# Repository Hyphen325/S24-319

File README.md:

This project is all of the lab work from ECE 319k and it's associated projects

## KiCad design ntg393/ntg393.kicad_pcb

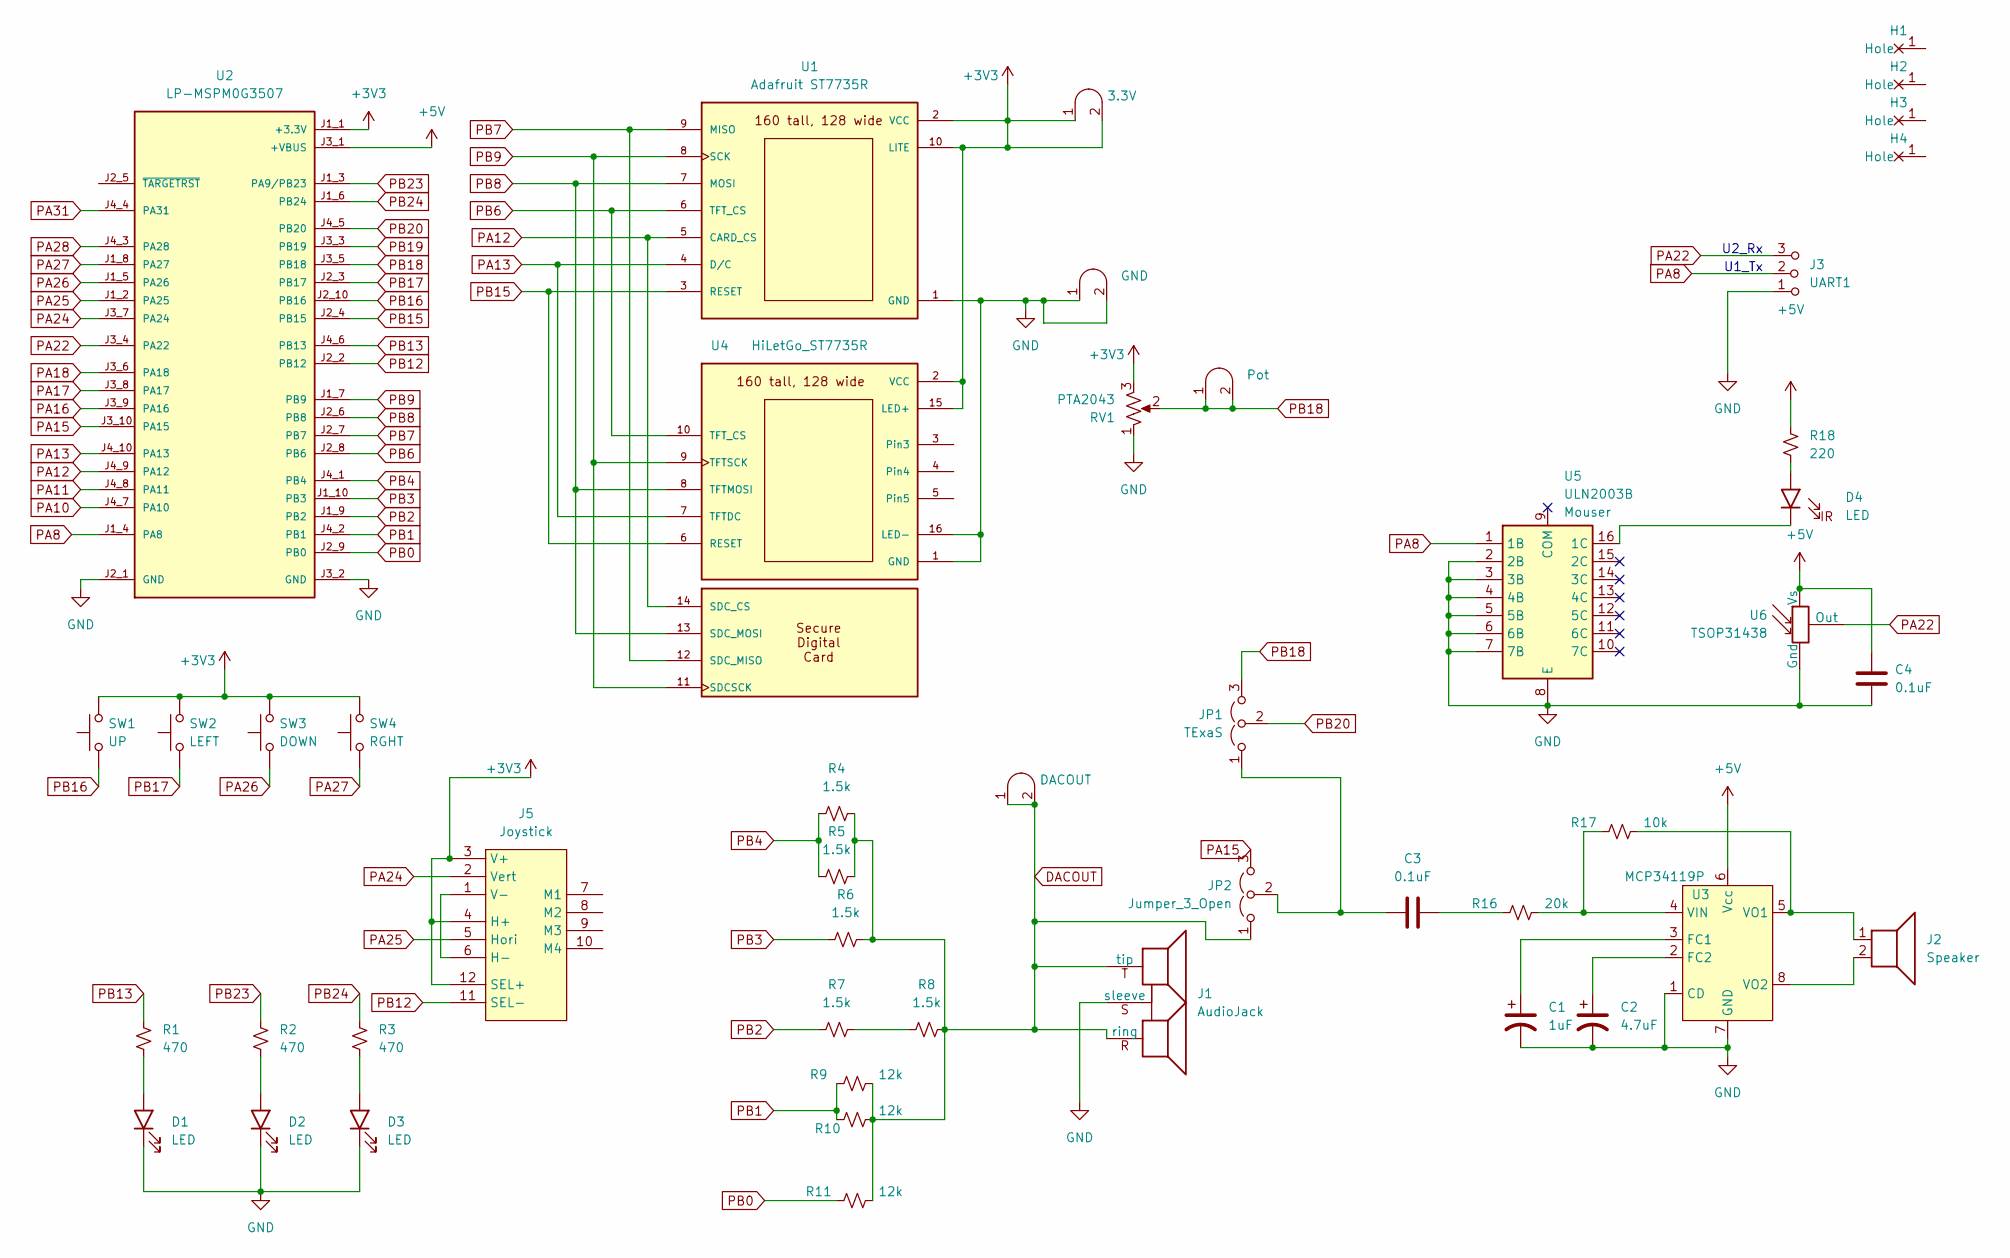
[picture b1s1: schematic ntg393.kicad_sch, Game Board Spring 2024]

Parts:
C1: 1uF; CP_Radial_Tantal200mil
C2: 4.7uF; CP_Radial_Tantal200mil
C3, C4: 0.1uF; C_Axial_200mil
D1, D2, D3, D4: LED; LED_D5.0mm
H1, H2, H3, H4: MountingHole_4_40
J1: AudioJack; Jack_3.5mm_CUI_SJ1-3523N_Horizontal
J2: Speaker; PinHeader_1x02_P2.54mm_Vertical
J3: UART1; PinHeader_1x03_P2.54mm_Vertical
J4: Pot; Testpoint_1x02_P2.54mm
J5: Joystick; SparkfunJoystick
J6: GND; Testpoint_1x02_P2.54mm
J7: DACOUT; Testpoint_1x02_P2.54mm
JP1: TExaS; PinHeader_1x03_P2.54mm_Vertical
JP2: Jumper_3_Open; PinHeader_1x03_P2.54mm_Vertical
R1, R2, R3: 470; R_Axial_DIN0204_L3.6mm_D1.6mm_P7.62mm_Horizontal
R4, R5, R6, R7, R8: 1.5k; R_Axial_DIN0204_L3.6mm_D1.6mm_P7.62mm_Horizontal
R9, R10, R11: 12k; R_Axial_DIN0204_L3.6mm_D1.6mm_P7.62mm_Horizontal
R16: 20k; R_Axial_DIN0204_L3.6mm_D1.6mm_P7.62mm_Horizontal
R17: 10k; R_Axial_DIN0204_L3.6mm_D1.6mm_P7.62mm_Horizontal
R18: 220; R_Axial_DIN0204_L3.6mm_D1.6mm_P7.62mm_Horizontal
RV1: PTA2043; PTA2043pot
SW1: UP; SW_PUSH_6mm
SW2: LEFT; SW_PUSH_6mm
SW3: DOWN; SW_PUSH_6mm
SW4: RGHT; SW_PUSH_6mm
TP1: 3.3V; Testpoint_1x02_P2.54mm
U1: Adafruit ST7735R; adafruit_st7735r
U2: LP-MSPM0G3507; ti_LP_MSPM0G3507
U3: MCP34119P; DIP-8_W7.62mm_LongPads
U4: HiLetGo_ST7735R; hiletgo_st7735r
U5: ULN2003B; DIP-16_W7.62mm
U6: TSOP31438

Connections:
+3V3: J5.3 (V+), J5.4 (H+), J5.12 (SEL+), RV1.3, SW1.2, SW2.2, SW3.2, SW4.2, TP1.1 (A), TP1.2 (B), U1.2 (VCC), U1.10 (LITE), U2.J1_1 (+3.3V), U4.2 (VCC), U4.15 (LED+)
+5V: C4.1, R18.1, U2.J3_1 (+VBUS), U3.6 (Vcc), U6.2 (Vs)
DACOUT: J1.R (ring), J1.T (tip), J7.1 (A), J7.2 (B), JP2.1 (A), R4.1, R5.1, R6.1, R8.1, R9.1, R10.1, R11.1
GND: C1.2, C2.2, C4.2, D1.1 (K), D2.1 (K), D3.1 (K), J1.S (sleeve), J3.1 (A), J6.1 (A), J6.2 (B), RV1.1, U1.1 (GND), U2.J2_1 (GND), U2.J3_2 (GND), U3.1 (CD), U3.7 (GND), U4.1 (GND), U4.16 (LED-), U5.2 (2B), U5.3 (3B), U5.4 (4B), U5.5 (5B), U5.6 (6B), U5.7 (7B), U5.8 (E), U6.1 (Gnd)
unnamed: C3.2, R16.2
unnamed: D1.2 (A), R1.2
unnamed: D2.2 (A), R2.2
unnamed: D3.2 (A), R3.2
unnamed: D4.2 (A), R18.2
unnamed: D4.1 (K), U5.16 (1C)
unnamed: J5.1 (V-), J5.6 (H-)
unnamed: C3.1, JP1.1 (A), JP2.2 (C)
unnamed: R7.1, R8.2
unnamed: C1.1, U3.3 (FC1)
unnamed: C2.1, U3.2 (FC2)
unnamed: R16.1, R17.2, U3.4 (VIN)
unnamed: J2.1, R17.1, U3.5 (VO1)
unnamed: J2.2, U3.8 (VO2)
PA8: J3.2 (B), U2.J1_4 (PA8), U5.1 (1B)
PA10: U2.J4_7 (PA10)
PA11: U2.J4_8 (PA11)
PA12: U1.5 (CARD_CS), U2.J4_9 (PA12), U4.14 (SDC_CS)
PA13: U1.4 (D/C), U2.J4_10 (PA13), U4.7 (TFTDC)
PA15: JP2.3 (B), U2.J3_10 (PA15)
PA16: U2.J3_9 (PA16)
PA17: U2.J3_8 (PA17)
PA18: U2.J3_6 (PA18)
PA22: J3.3 (C), U2.J3_4 (PA22), U6.3 (Out)
PA24: J5.2 (Vert), U2.J3_7 (PA24)
PA25: J5.5 (Hori), U2.J1_2 (PA25)
PA26: SW3.1, U2.J1_5 (PA26)
PA27: SW4.1, U2.J1_8 (PA27)
PA28: U2.J4_3 (PA28)
PA31: U2.J4_4 (PA31)
PB0: R11.2, U2.J2_9 (PB0)
PB1: R9.2, R10.2, U2.J4_2 (PB1)
PB2: R7.2, U2.J1_9 (PB2)
PB3: R6.2, U2.J1_10 (PB3)
PB4: R4.2, R5.2, U2.J4_1 (PB4)
PB6: U1.6 (TFT_CS), U2.J2_8 (PB6), U4.10 (TFT_CS)
PB7: U1.9 (MISO), U2.J2_7 (PB7), U4.12 (SDC_MISO)
PB8: U1.7 (MOSI), U2.J2_6 (PB8), U4.8 (TFTMOSI), U4.13 (SDC_MOSI)
PB9: U1.8 (SCK), U2.J1_7 (PB9), U4.9 (TFTSCK), U4.11 (SDCSCK)
PB12: J5.11 (SEL-), U2.J2_2 (PB12)
PB13: R1.1, U2.J4_6 (PB13)
PB15: U1.3 (RESET), U2.J2_4 (PB15), U4.6 (RESET)
PB16: SW1.1, U2.J2_10 (PB16)
PB17: SW2.1, U2.J2_3 (PB17)
PB18: J4.1 (A), J4.2 (B), JP1.3 (B), RV1.2, U2.J3_5 (PB18)
PB19: U2.J3_3 (PB19)
PB20: JP1.2 (C), U2.J4_5 (PB20)
PB23: R2.1, U2.J1_3 (PA9/PB23)
PB24: R3.1, U2.J1_6 (PB24)

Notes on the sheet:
U2_Rx
U1_Tx

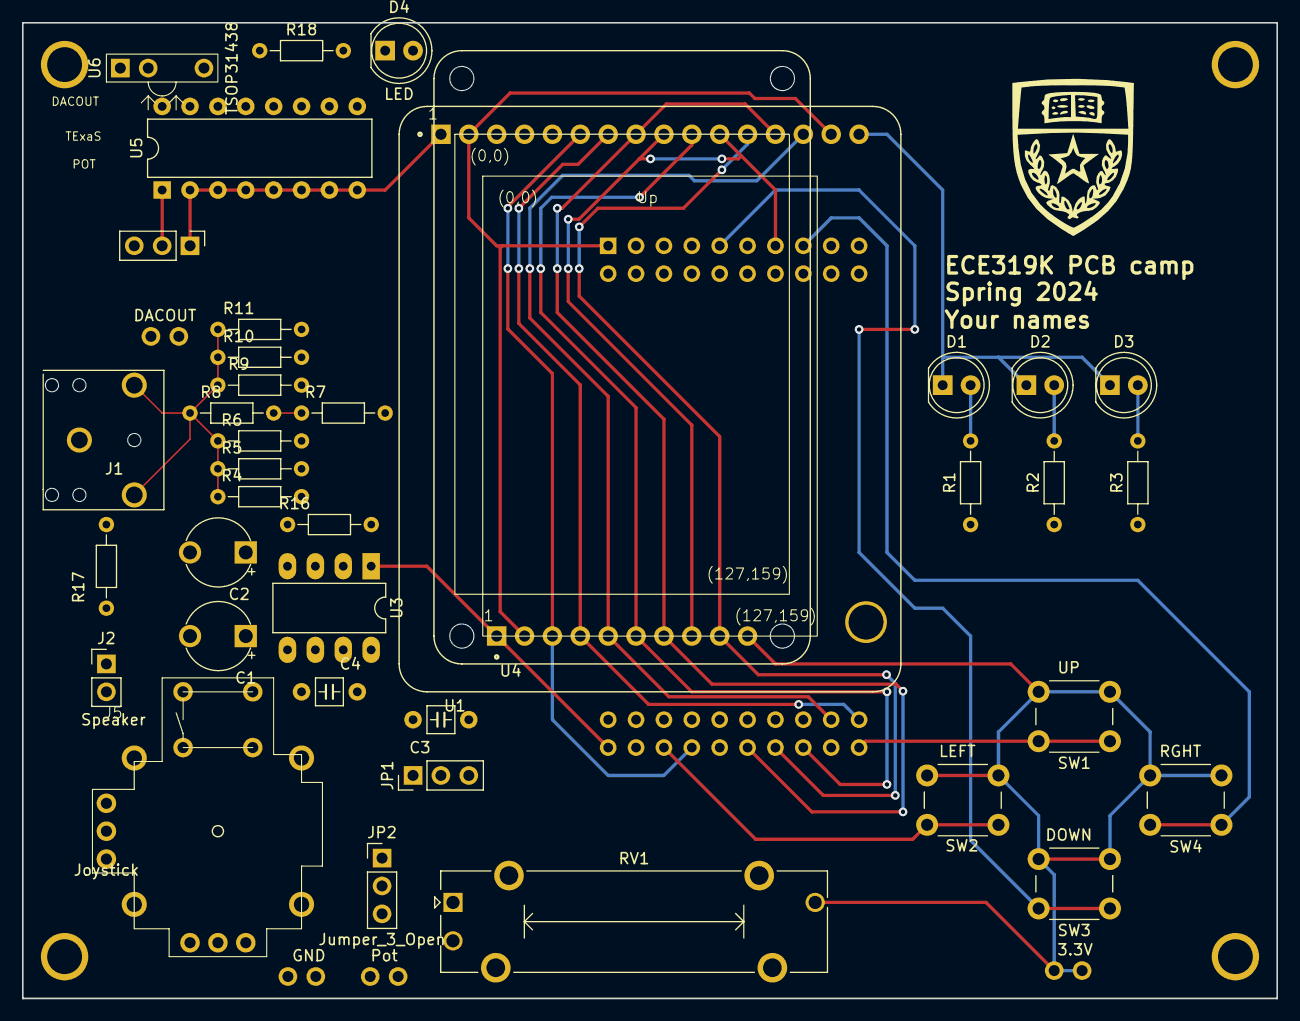
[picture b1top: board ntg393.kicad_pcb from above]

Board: 2 copper layers, 114.3 x 88.9 mm, 47 parts (1 on the bottom side), 45 nets.

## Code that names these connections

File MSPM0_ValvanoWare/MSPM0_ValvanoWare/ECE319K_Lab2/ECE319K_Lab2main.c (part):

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// PA11 is UART0 Rx    index 21 in IOMUX PINCM table
// Insert jumper J25: Connects PA10 to XDS_UART
// Insert jumper J26: Connects PA11 to XDS_UART
// Switch input PB2 PB1 or PB0
// LED output PB18 PB17 or PB16
// logic analyzer pins PB18 PB17 PB16 PB2 PB1 PB0
// analog scope pin PB20, channel 6
uint32_t Score;

uint32_t M;
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int Mode1=0; // randomly assigns 0 to 3
int Mode2=0; // randomly assigns 0 to 3
const char ChangeProblem[4][80]={
  "\n\rImplement the Change switch using PB0",  // Mode0=0
  "\n\rImplement the Change switch using PB1",  // Mode0=1
  "\n\rImplement the Change switch using PB2",  // Mode0=2
  "\n\rImplement the Change switch using PB3"   // Mode0=3
};
const uint32_t InMux[4]={PB0INDEX,PB1INDEX,PB2INDEX,PB3INDEX};
const uint32_t ChangeMask[4]={1,2,4,8};
const char LEDProblem[3][80]={
  "\n\rImplement the LED on PB16",               // Mode1=0
  "\n\rImplement the LED on PB17",               // Mode1=1
  "\n\rImplement the LED on PB18"                // Mode1=2
};
const uint32_t OutMux[3]={PB16INDEX,PB17INDEX,PB18INDEX};
const uint32_t LEDMask[3]={(1<<16),(1<<17),(1<<18)};
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   //  UART_Out(test);
     UART_Out(ADC_In(TExaSadc)); // 8-bit data at 10 kHz
  }else{
     // logic analyzer for PB18-16 outputs, PB3-0 input
    UART_Out(0x80|((GPIOB->DOUT31_0&0x70000)>>12)|(GPIOB->DIN31_0&0x0F)); // 7-bit digital data at 10 kHz
  }
}
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  }

  if(Phase == 2){//  2 debug with scope,
    ADC_Init(ADC0,6,ADCVREF_VDDA); // PB20, 0 to 3.3V range
    ADC_Start(ADC0);
  //  ADC0_Init(6,ADCVREF_VDDA); // PB20, 0 to 3.3V range
    TimerG7_IntArm(Clock_Freq()/10000,1,3); // G7 is in Power domain PD2
    __enable_irq();
    return;
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
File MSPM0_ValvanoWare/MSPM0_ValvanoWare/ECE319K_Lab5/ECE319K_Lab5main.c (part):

/* ECE319K_Lab5main.c
 * Digital Piano using a Digital to Analog Converter
 * December 28, 2023
 * 5-bit binary-weighted DAC connected to PB4-PB0
 * 4-bit keyboard connected to PB19-PB16
*/

#include <ti/devices/msp/msp.h>
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  }
}
// use main2b to perform static testing of DAC, if you do not have a voltmeter
// attach PB20 (scope uses PB20 as ADC input) to your DACout
// TExaSdisplay scope uses TimerG7, ADC0
// To use the scope, there can be no breakpoints in your code
int main2b(void){ // main2b
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}
// use main3 to perform dynamic testing of DAC,
// In lab, attach your DACout to the real scope
// If you do not have a scope attach PB20 (scope uses PB20 as ADC input) to your DACout
// TExaSdisplay scope uses TimerG7, ADC0
// To perform dynamic testing, there can be no breakpoints in your code
// DACout will be a monotonic ramp with period 32ms,
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
// use main5 to debug your system
// In lab, attach your DACout to the real scope
// If you do not have a scope attach PB20 (scope uses PB20 as ADC input) to your DACout
// TExaSdisplay scope uses TimerG7, ADC0
// To perform dynamic testing, there can be no breakpoints in your code
// DACout will be a sine wave with period/frequency depending on which key is pressed
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
// use main6 to debug/grade your final system
// In lab, attach your DACout to the real scope
// If you do not have a scope attach PB20 (scope uses PB20 as ADC input) to your DACout
// TExaSdisplay scope uses TimerG7, ADC0
// To perform dynamic testing, there can be no breakpoints in your code
// DACout will be a sine wave with period/frequency depending on which key is pressed
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    Clock_Delay(800000); // 10ms, to debounce switch
  }
}
// To grade you must connect PB20 to your DACout
// Run main6 with Lab5Grader(3);   // Grader
// Observe Terminal window

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
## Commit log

2024-04-02 added lab work
2024-04-02 Added .pretty files from PCB camp
2024-04-07 updated files
2024-04-08 whatever I was working on
2024-04-08 Update IRxmt.cpp with good clock
2024-04-14 updating files

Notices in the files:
MSPM0_ValvanoWare/MSPM0_ValvanoWare/ECE319K_Lab2/ECE319K_Lab2main.c:
Copyright 2023 by Jonathan W. Valvano, valvano@mail.utexas.edu
